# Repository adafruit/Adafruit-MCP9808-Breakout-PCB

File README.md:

## Adafruit MCP9808 High Accuracy I2C Temperature Sensor Breakout PCB
<a href="http://www.adafruit.com/products/5027"><br/>
<a href="http://www.adafruit.com/products/1782"><br/>
Click here to purchase one from the Adafruit shop</a>

This I2C digital temperature sensor is one of the more accurate/precise we've ever seen, with a typical accuracy of ±0.25°C over the sensor's -40°C to +125°C range and precision of +0.0625°C. They work great with any microcontroller using standard i2c. There are 3 address pins so you can connect up to 8 to a single I2C bus without address collisions. Best of all, a wide voltage range makes it usable with 2.7V to 5.5V logic!

Unlike the DS18B20, this sensor does not come in through-hole package so we placed this small sensor on a breakout board PCB for easy use. The PCB includes mounting holes, and pull down resistors for the 3 address pins. We even wrote a lovely little tutorial and library that will work with Arduino or CircuitPython. You'll be up and running in 15 minutes or less.

PCB files for the Adafruit MCP9808 Breakout. The format is EagleCAD schematic and board layout
- https://www.adafruit.com/products/1782

### License

Adafruit invests time and resources providing this open source design, please support Adafruit and open-source hardware by purchasing products from [Adafruit](https://www.adafruit.com)!

All text above must be included in any redistribution

Designed by Limor Fried/Ladyada for Adafruit Industries.
Creative Commons Attribution/Share-Alike, all text above must be included in any redistribution. 
See license.txt for additional information.

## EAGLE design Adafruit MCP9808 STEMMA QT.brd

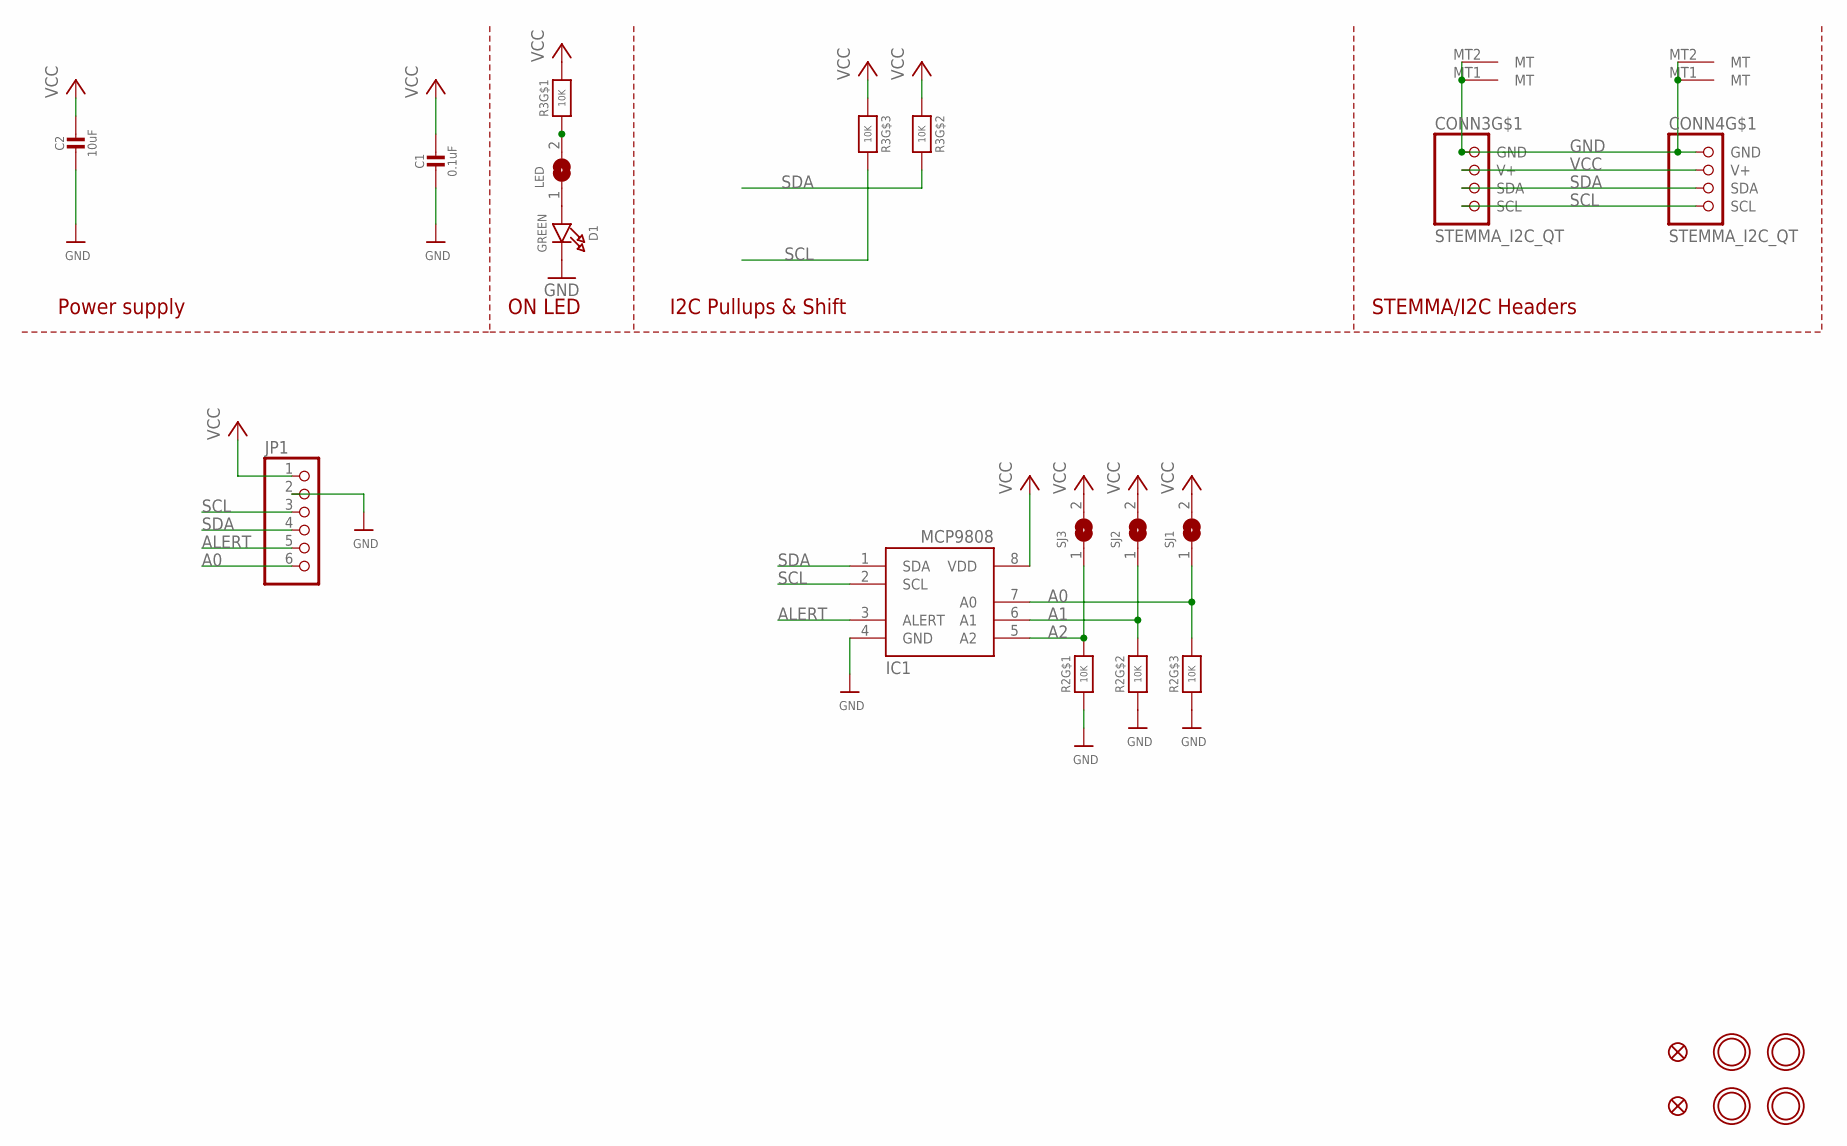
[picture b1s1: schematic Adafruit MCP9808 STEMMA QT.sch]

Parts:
C1: 0.1uF; 0603-NO
C2: 10uF; 0805-NO
CONN3, CONN4: STEMMA_I2C_QT; JST_SH4
D1: GREEN; CHIPLED_0603_NOOUTLINE
FID3, FID4: FIDUCIAL_1MM
IC1: MCP9808-E/MS; MSOP8_0.65MM
JP1: HEADER-1X670MIL; 1X06_ROUND_70
LED: SOLDERJUMPERCLOSED; SOLDERJUMPER_CLOSEDWIRE
R2, R3: 10K; RESPACK_4X0603
SJ1, SJ2, SJ3: SOLDERJUMPER; SOLDERJUMPER_ARROW_NOPASTE
U$1, U$17, U$19, U$21: MOUNTINGHOLE2.5; MOUNTINGHOLE_2.5_PLATED

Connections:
A0: IC1.7 (A0), JP1.6, R2.6 (2), SJ1.1
A1: IC1.6 (A1), R2.7 (2), SJ2.1
A2: IC1.5 (A2), R2.8 (2), SJ3.1
ALERT: IC1.3 (ALERT), JP1.5
GND: C1.2, C2.2, CONN3.1 (GND), CONN3.MT1 (MT), CONN3.MT2 (MT), CONN4.1 (GND), CONN4.MT1 (MT), CONN4.MT2 (MT), D1.C, IC1.4 (GND), JP1.2, R2.1, R2.2 (1), R2.3 (1)
unnamed: LED.2, R3.1
unnamed: D1.A, LED.1
SCL: CONN3.4 (SCL), CONN4.4 (SCL), IC1.2 (SCL), JP1.3, R3.6 (2)
SDA: CONN3.3 (SDA), CONN4.3 (SDA), IC1.1 (SDA), JP1.4, R3.7 (2)
VCC: C1.1, C2.1, CONN3.2 (V+), CONN4.2 (V+), IC1.8 (VDD), JP1.1, R3.2 (1), R3.3 (1), R3.8 (2), SJ1.2, SJ2.2, SJ3.2

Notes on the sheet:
I2C Pullups & Shift
STEMMA/I2C Headers
ON LED
Power supply

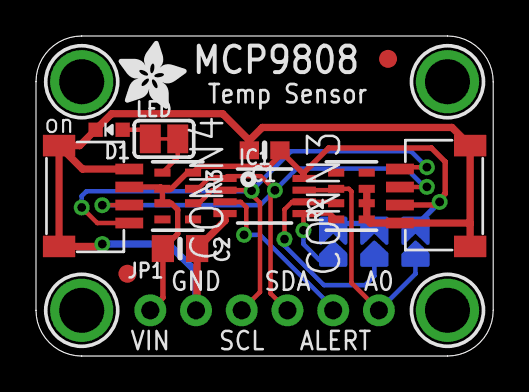
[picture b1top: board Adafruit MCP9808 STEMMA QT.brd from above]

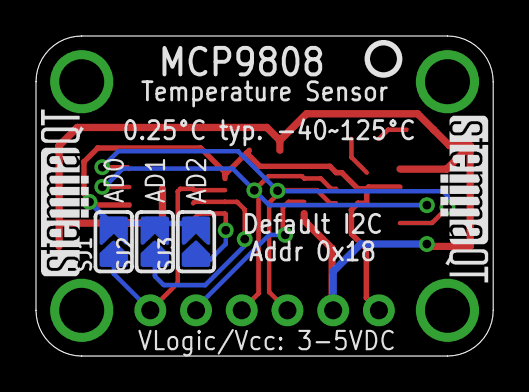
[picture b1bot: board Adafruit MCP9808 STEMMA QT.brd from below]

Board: 2 copper layers, 25.4 x 17.8 mm, 23 parts (6 on the bottom side), 10 nets.

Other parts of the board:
U$22: ADAFRUIT_3.5MM
U$25: PCBFEAT-REV-040
U$30, U$31: STEMMAQT

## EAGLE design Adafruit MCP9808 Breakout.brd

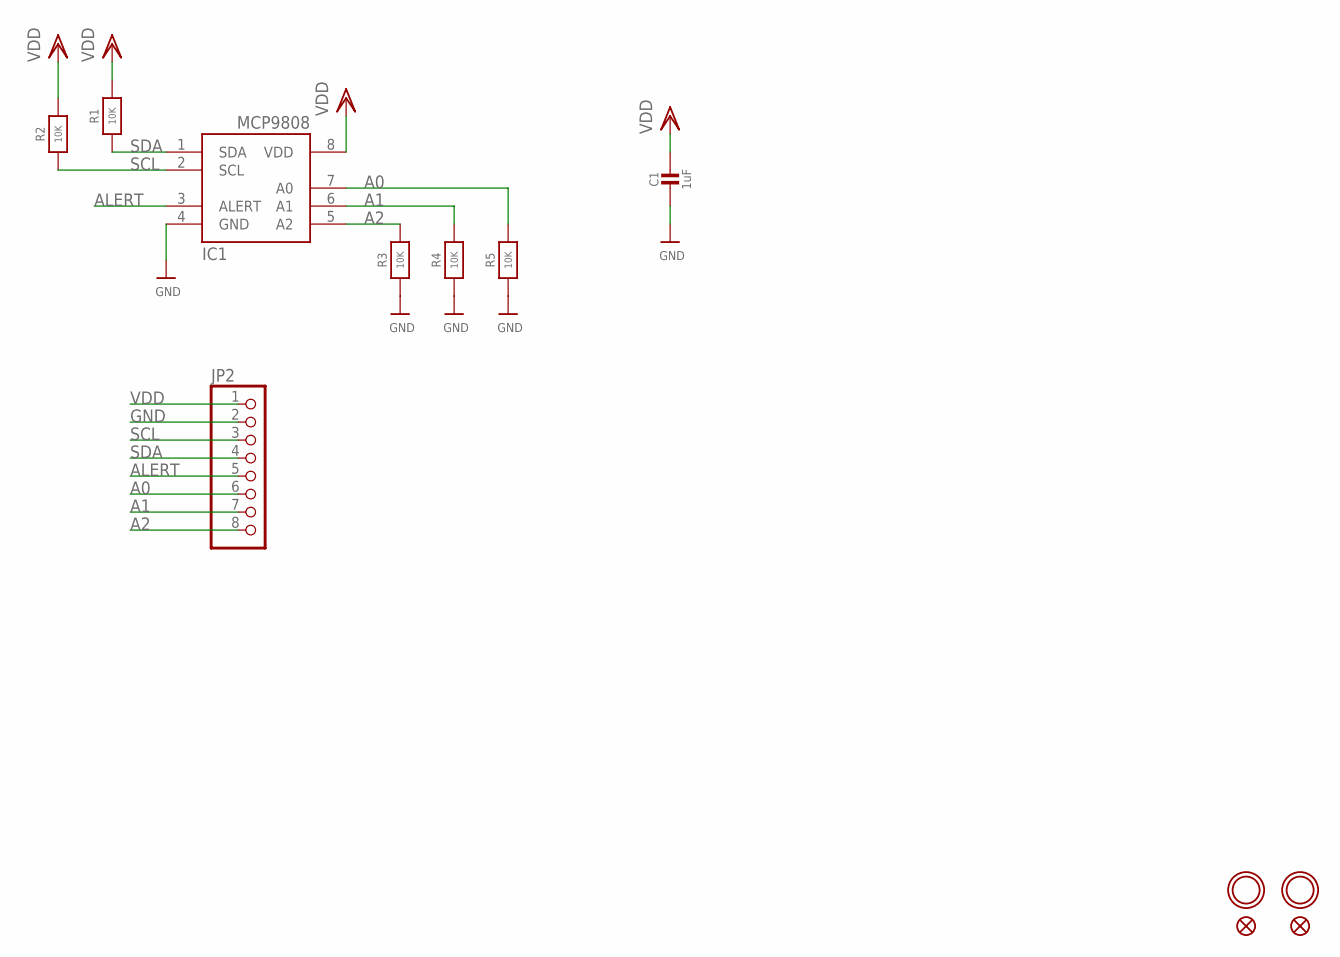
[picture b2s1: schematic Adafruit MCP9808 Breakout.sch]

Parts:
C1: 1uF; _0805MP
FID1, FID2: FIDUCIAL""; FIDUCIAL_1MM
IC1: MCP9808-E/MS; MSOP8_0.65MM
JP2: HEADER-1X870MIL; 1X08_ROUND_70
R1, R2, R3, R4, R5: 10K; 0805-NO
U$3, U$5: MOUNTINGHOLE2.5; MOUNTINGHOLE_2.5_PLATED

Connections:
A0: IC1.7 (A0), JP2.6, R5.2
A1: IC1.6 (A1), JP2.7, R4.2
A2: IC1.5 (A2), JP2.8, R3.2
ALERT: IC1.3 (ALERT), JP2.5
GND: C1.2, IC1.4 (GND), JP2.2, R3.1, R4.1, R5.1
SCL: IC1.2 (SCL), JP2.3, R2.1
SDA: IC1.1 (SDA), JP2.4, R1.1
VDD: C1.1, IC1.8 (VDD), JP2.1, R1.2, R2.2

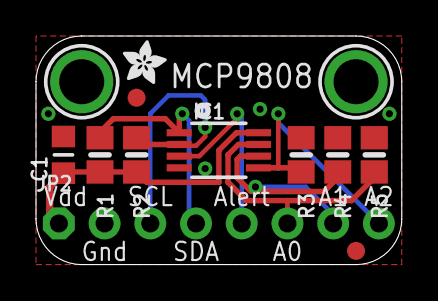
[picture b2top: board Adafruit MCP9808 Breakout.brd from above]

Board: 2 copper layers, 20.3 x 12.7 mm, 13 parts (0 on the bottom side), 8 nets.

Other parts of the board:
U$4: ADAFRUIT_2.5MM

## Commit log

2016-09-09 init
2021-06-23 Add board files.
2021-06-23 Upload asset.

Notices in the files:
parts and their libraries:
microbuilder: This work is placed in the public domain, and may be freely used for commercial and non-commercial work with the following conditions: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
